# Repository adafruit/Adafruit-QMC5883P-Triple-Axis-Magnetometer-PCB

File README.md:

## Adafruit QMC5883P - Triple Axis Magnetometer - STEMMA QT PCB

<a href="http://www.adafruit.com/products/6388"><br/>
Click here to purchase one from the Adafruit shop</a>

PCB files for the Adafruit QMC5883P - Triple Axis Magnetometer - STEMMA QT. 

Format is EagleCAD schematic and board layout
* https://www.adafruit.com/product/6388

### Description

Sense the magnetic fields that surround us with this handy triple-axis magnetometer (compass) module. Magnetometers can sense where the strongest magnetic force is coming from, generally used to detect magnetic north, but can also be used for measuring magnetic fields. This sensor tends to be paired with a 6-DoF (degree of freedom) accelerometer/gyroscope to create a 9-DoF inertial measurement unit that can detect its orientation in real-space thanks to Earth's stable magnetic field.

We based this breakout on the QMC5883P, a magnetometer we see used in may Quadcopter and robotic builds. This compact sensor uses I2C to communicate, and it's very easy to use. Simply download our library and connect the SCL pin to your I2C clock pin, and SDA pin to your I2C data pin and upload our test program to read out magnetic field data.

This sensor can sense ranges from +-2 Gauss (+- 200 uTesla) up to +-30 gauss (+- 3000 uT or 3.0 mT). With 16-bit ADC and settings for over-sampling and down-sampling, you can set it up to get just the right range and precision.

To make life easier so you can focus on your important work, we've taken the QMC5883P and put it onto a breakout PCB along with support circuitry to let you use this little wonder with 3.3V (Feather/Raspberry Pi) or 5V (Arduino/ Metro328) logic levels. Additionally, since it speaks I2C you can easily connect it up with two wires (plus power and ground!).  We've even included SparkFun qwiic compatible STEMMA QT connectors for the I2C bus so you don't even need to solder! Just wire up to your favorite micro and you can use our CircuitPython/Python or Arduino drivers to easily interface with the QMC5883P and get magnetic measurements ASAP. QT Cable is not included, but we have a variety in the shop. 

It's fully assembled and tested.  Comes with a bit of 0.1" standard header in case you want to use it with a breadboard or perfboard.  Four 2.5mm (0.1") mounting holes for easy attachment.

### License

Adafruit invests time and resources providing this open source design, please support Adafruit and open-source hardware by purchasing products from [Adafruit](https://www.adafruit.com)!

Designed by Limor Fried/Ladyada for Adafruit Industries.

Creative Commons Attribution/Share-Alike, all text above must be included in any redistribution. 
See license.txt for additional details.

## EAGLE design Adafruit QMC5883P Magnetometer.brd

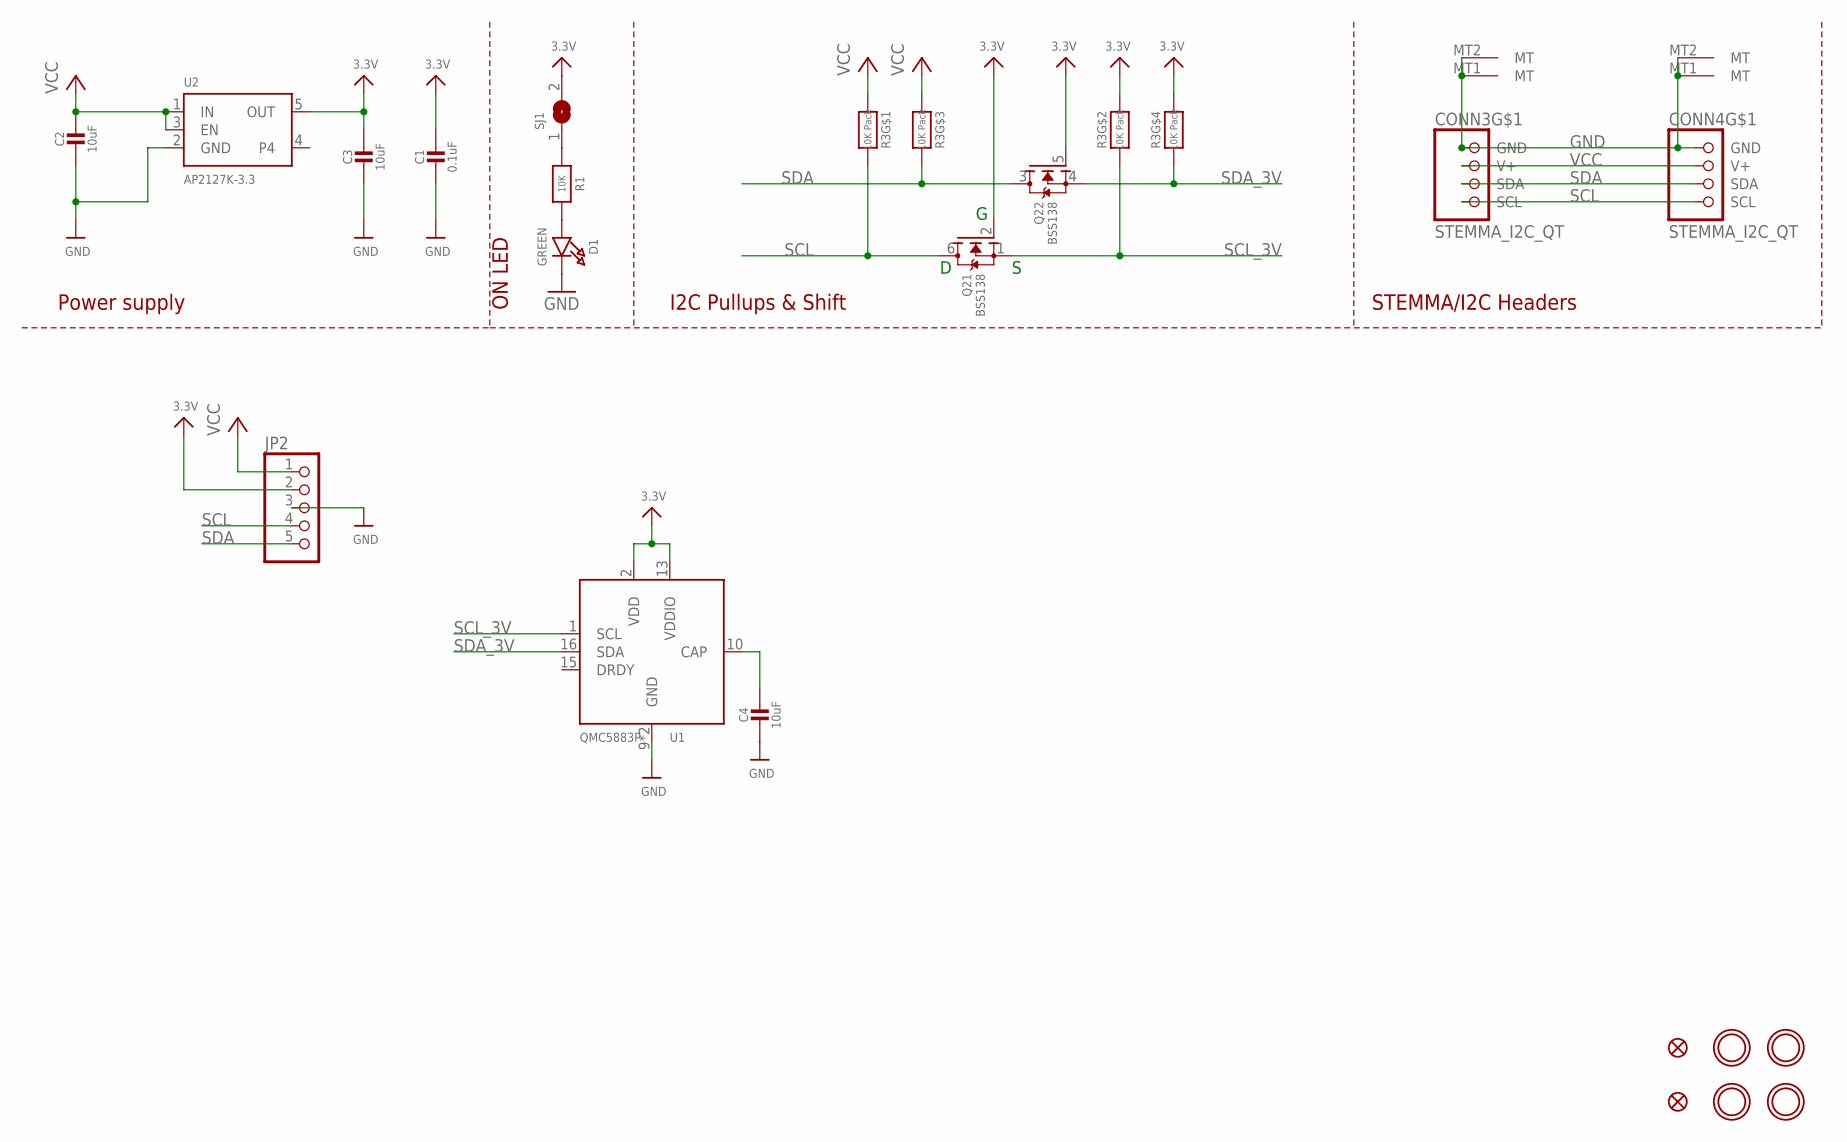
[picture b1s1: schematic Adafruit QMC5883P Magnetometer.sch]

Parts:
C1: 0.1uF; 0603-NO
C2, C3, C4: 10uF; 0805-NO
CONN3, CONN4: STEMMA_I2C_QT; JST_SH4
D1: GREEN; CHIPLED_0603_NOOUTLINE
FID3, FID4: FIDUCIAL_0.5MM
JP2: HEADER-1X570MIL; 1X05_ROUND_70
Q2: BSS138; SOT363
R1: 10K; 0603-NO
R3: 10K Pack; RESPACK_4X0603
SJ1: SOLDERJUMPERCLOSED; SOLDERJUMPER_CLOSEDWIRE
U1: QMC5883P; HMC5883L
U2: AP2127K-3.3; SOT23-5
U$1, U$17, U$19, U$21: MOUNTINGHOLE2.5; MOUNTINGHOLE_2.5_PLATED

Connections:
3.3V: C1.1, C3.1, JP2.2, Q2.2 (G), Q2.5 (G), R3.2 (1), R3.4 (1), SJ1.2, U1.2 (VDD), U1.13 (VDDIO), U2.5 (OUT)
GND: C1.2, C2.2, C3.2, C4.2, CONN3.1 (GND), CONN3.MT1 (MT), CONN3.MT2 (MT), CONN4.1 (GND), CONN4.MT1 (MT), CONN4.MT2 (MT), D1.C, JP2.3, U1.9 (GND), U1.11 (GND), U2.2 (GND)
unnamed: D1.A, R1.2
unnamed: R1.1, SJ1.1
unnamed: C4.1, U1.10 (CAP)
SCL: CONN3.4 (SCL), CONN4.4 (SCL), JP2.4, Q2.6 (D), R3.8 (2)
SCL_3V: Q2.1 (S), R3.7 (2), U1.1 (SCL)
SDA: CONN3.3 (SDA), CONN4.3 (SDA), JP2.5, Q2.3 (D), R3.6 (2)
SDA_3V: Q2.4 (S), R3.5 (2), U1.16 (SDA)
VCC: C2.1, CONN3.2 (V+), CONN4.2 (V+), JP2.1, R3.1, R3.3 (1), U2.1 (IN), U2.3 (EN)

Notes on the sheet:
I2C Pullups & Shift
STEMMA/I2C Headers
ON LED
Power supply

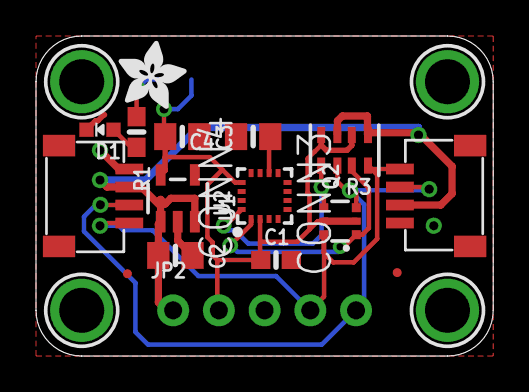
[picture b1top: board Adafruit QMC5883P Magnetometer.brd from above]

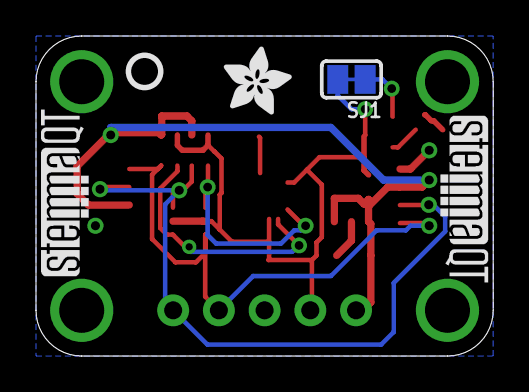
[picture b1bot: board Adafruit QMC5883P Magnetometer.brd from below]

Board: 2 copper layers, 25.4 x 17.8 mm, 37 parts (9 on the bottom side), 10 nets.

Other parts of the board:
PLABEL0: PLABEL0
PLABEL1: PLABEL1
PLABEL2: PLABEL2
PLABEL3: PLABEL3
PLABEL4: PLABEL4
PLABEL5: PLABEL5
PLABEL6: PLABEL6
PLABEL7: PLABEL7
PLABEL8: PLABEL8
PLABEL10: PLABEL10
PLABEL11: PLABEL11
PLABEL12: PLABEL12
U$9, U$22: ADAFRUIT_3.5MM
U$25: PCBFEAT-REV-040
U$30, U$31: STEMMAQT

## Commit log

2025-08-06 cookiecutter

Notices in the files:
parts and their libraries:
microbuilder: This work is placed in the public domain, and may be freely used for commercial and non-commercial work with the following conditions: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
